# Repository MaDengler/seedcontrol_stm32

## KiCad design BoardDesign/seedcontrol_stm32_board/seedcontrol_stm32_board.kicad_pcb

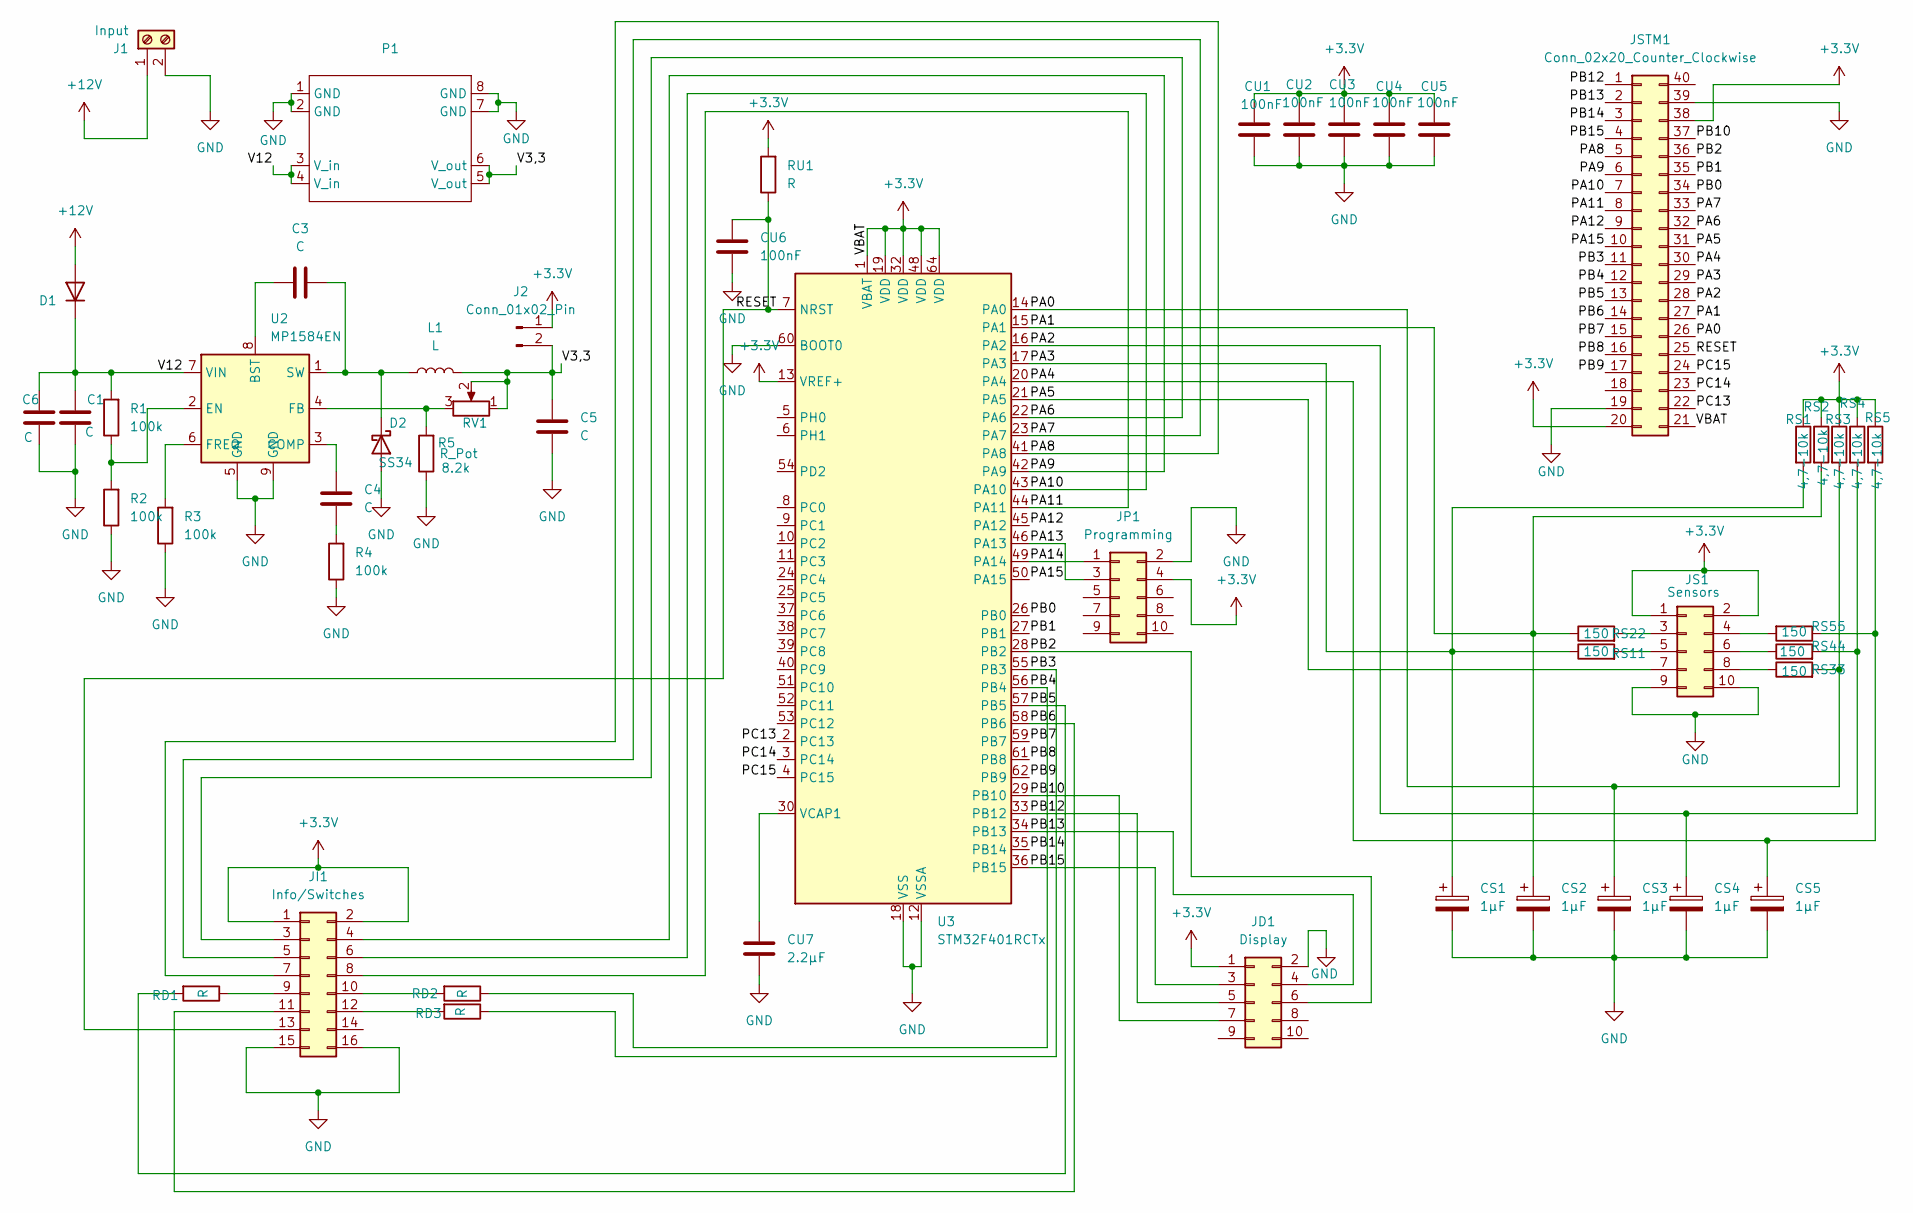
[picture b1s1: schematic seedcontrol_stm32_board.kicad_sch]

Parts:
C1, C3, C4: C; C_0603_1608Metric
C5, C6: C; C_1206_3216Metric
CS1, CS2, CS3, CS4, CS5: 1µF; C_Rect_L10.0mm_W3.0mm_P7.50mm_MKS4
CU1, CU2, CU3, CU4, CU5, CU6: 100nF; C_0402_1005Metric
CU7: 2.2µF; C_0402_1005Metric
D1: D_DO-41_SOD81_P12.70mm_Horizontal
D2: SS34; D_SMA
J1: Input; TerminalBlock_Altech_AK300-2_P5.00mm
J2: Conn_01x02_Pin; PinHeader_1x02_P2.54mm_Vertical
JD1: Display; PinHeader_2x05_P2.54mm_Vertical
JI1: Info/Switches; PinHeader_2x08_P2.54mm_Vertical
JP1: Programming; PinHeader_2x05_P2.54mm_Vertical
JS1: Sensors; PinHeader_2x05_P2.54mm_Vertical
JSTM1: Conn_02x20_Counter_Clockwise; STM32_Blackpill_header
L1: L; L_Bourns_SRP7028A_7.3x6.6mm
P1: Voltage_converter
R1, R2, R3, R4: 100k; R_0603_1608Metric
R5: 8.2k; R_0603_1608Metric
RD1, RD2, RD3: R; R_0603_1608Metric
RS1, RS2, RS3, RS4, RS5: 4,7-10k; R_Axial_DIN0309_L9.0mm_D3.2mm_P12.70mm_Horizontal
RS11, RS22, RS33, RS44, RS55: 150; R_Axial_DIN0309_L9.0mm_D3.2mm_P12.70mm_Horizontal
RU1: R; R_0603_1608Metric
RV1: R_Pot; Potentiometer_Bourns_TC33X_Vertical
U2: MP1584EN; SOIC-8-1EP_3.9x4.9mm_P1.27mm_EP2.62x3.51mm
U3: STM32F401RCTx; LQFP-64_10x10mm_P0.5mm

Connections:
+3.3V: CU1.2, CU2.2, CU3.2, CU4.2, CU5.2, J2.1, JD1.1, JI1.1, JI1.2, JP1.4, JS1.1, JS1.2, JSTM1.20, JSTM1.21, JSTM1.38, RS1.1, RS2.1, RS3.1, RS4.1, RS5.1, RU1.2, U3.1 (VBAT), U3.13 (VREF+), U3.19 (VDD), U3.32 (VDD), U3.48 (VDD), U3.64 (VDD)
+12V: D1.1 (A), J1.1
/PA0: CS3.1, JSTM1.26, RS3.2, RS33.2, U3.14 (PA0)
/PA1: CS2.1, JSTM1.27, RS2.2, RS22.1, U3.15 (PA1)
/PA2: CS4.1, JSTM1.28, RS4.2, RS44.2, U3.16 (PA2)
/PA3: CS1.1, JSTM1.29, RS1.2, RS11.1, U3.17 (PA3)
/PA4: CS5.1, JSTM1.30, RS5.2, RS55.1, U3.20 (PA4)
/PA5: JS1.7, JSTM1.31, U3.21 (PA5)
/PA6: JI1.3, JSTM1.32, U3.22 (PA6)
/PA7: JI1.5, JSTM1.33, U3.23 (PA7)
/PA8: JI1.7, JSTM1.5, U3.41 (PA8)
/PA9: JI1.4, JSTM1.6, U3.42 (PA9)
/PA10: JI1.6, JSTM1.7, U3.43 (PA10)
/PA11: JI1.8, JSTM1.8, U3.44 (PA11)
/PA12: JSTM1.9, U3.45 (PA12)
/PA13: JP1.3, U3.46 (PA13)
/PA14: JP1.1, U3.49 (PA14)
/PA15: JSTM1.10, U3.50 (PA15)
/PB0: JSTM1.34, U3.26 (PB0)
/PB1: JSTM1.35, U3.27 (PB1)
/PB2: JD1.6, JSTM1.36, U3.28 (PB2)
/PB3: JSTM1.11, RD3.1, U3.55 (PB3)
/PB4: JSTM1.12, RD2.1, U3.56 (PB4)
/PB5: JSTM1.13, RD1.2, U3.57 (PB5)
/PB6: JI1.11, JSTM1.14, U3.58 (PB6)
/PB7: JSTM1.15, U3.59 (PB7)
/PB8: JSTM1.16, U3.61 (PB8)
/PB9: JSTM1.17, U3.62 (PB9)
/PB10: JD1.7, JSTM1.37, U3.29 (PB10)
/PB12: JD1.5, JSTM1.1, U3.33 (PB12)
/PB13: JD1.4, JSTM1.2, U3.34 (PB13)
/PB14: JSTM1.3, U3.35 (PB14)
/PB15: JD1.3, JSTM1.4, U3.36 (PB15)
/PC13: JSTM1.22, U3.2 (PC13)
/PC14: JSTM1.23, U3.3 (PC14)
/PC15: JSTM1.24, U3.4 (PC15)
/RESET: CU6.2, JI1.13, JSTM1.25, RU1.1, U3.7 (NRST)
/V3,3: C5.2, J2.2, L1.2, P1.5 (V_out), P1.6 (V_out), RV1.1, RV1.2
/V12: C1.2, C6.2, D1.2 (K), P1.3 (V_in), P1.4 (V_in), R1.2, U2.7 (VIN)
GND: C1.1, C5.1, C6.1, CS1.2, CS2.2, CS3.2, CS4.2, CS5.2, CU1.1, CU2.1, CU3.1, CU4.1, CU5.1, CU6.1, CU7.1, D2.2 (A), J1.2, JD1.2, JI1.15, JI1.16, JP1.2, JS1.9, JS1.10, JSTM1.19, JSTM1.39, P1.1 (GND), P1.2 (GND), P1.7 (GND), P1.8 (GND), R2.1, R3.1, R4.1, R5.1, U2.5 (GND), U2.9 (GND), U3.12 (VSSA), U3.18 (VSS), U3.31 (VSS), U3.47 (VSS), U3.60 (BOOT0), U3.63 (VSS)
unnamed: C4.1, R4.2
unnamed: C3.2, D2.1 (K), L1.1, U2.1 (SW)
unnamed: JI1.9, RD1.1
unnamed: JI1.10, RD2.2
unnamed: JI1.12, RD3.2
unnamed: JS1.3, RS22.2
unnamed: JS1.4, RS55.2
unnamed: JS1.5, RS11.2
unnamed: JS1.6, RS44.1
unnamed: JS1.8, RS33.1
unnamed: C3.1, U2.8 (BST)
unnamed: C4.2, U2.3 (COMP)
unnamed: R1.1, R2.2, U2.2 (EN)
unnamed: R5.2, RV1.3, U2.4 (FB)
unnamed: R3.2, U2.6 (FREQ)
unnamed: CU7.2, U3.30 (VCAP1)

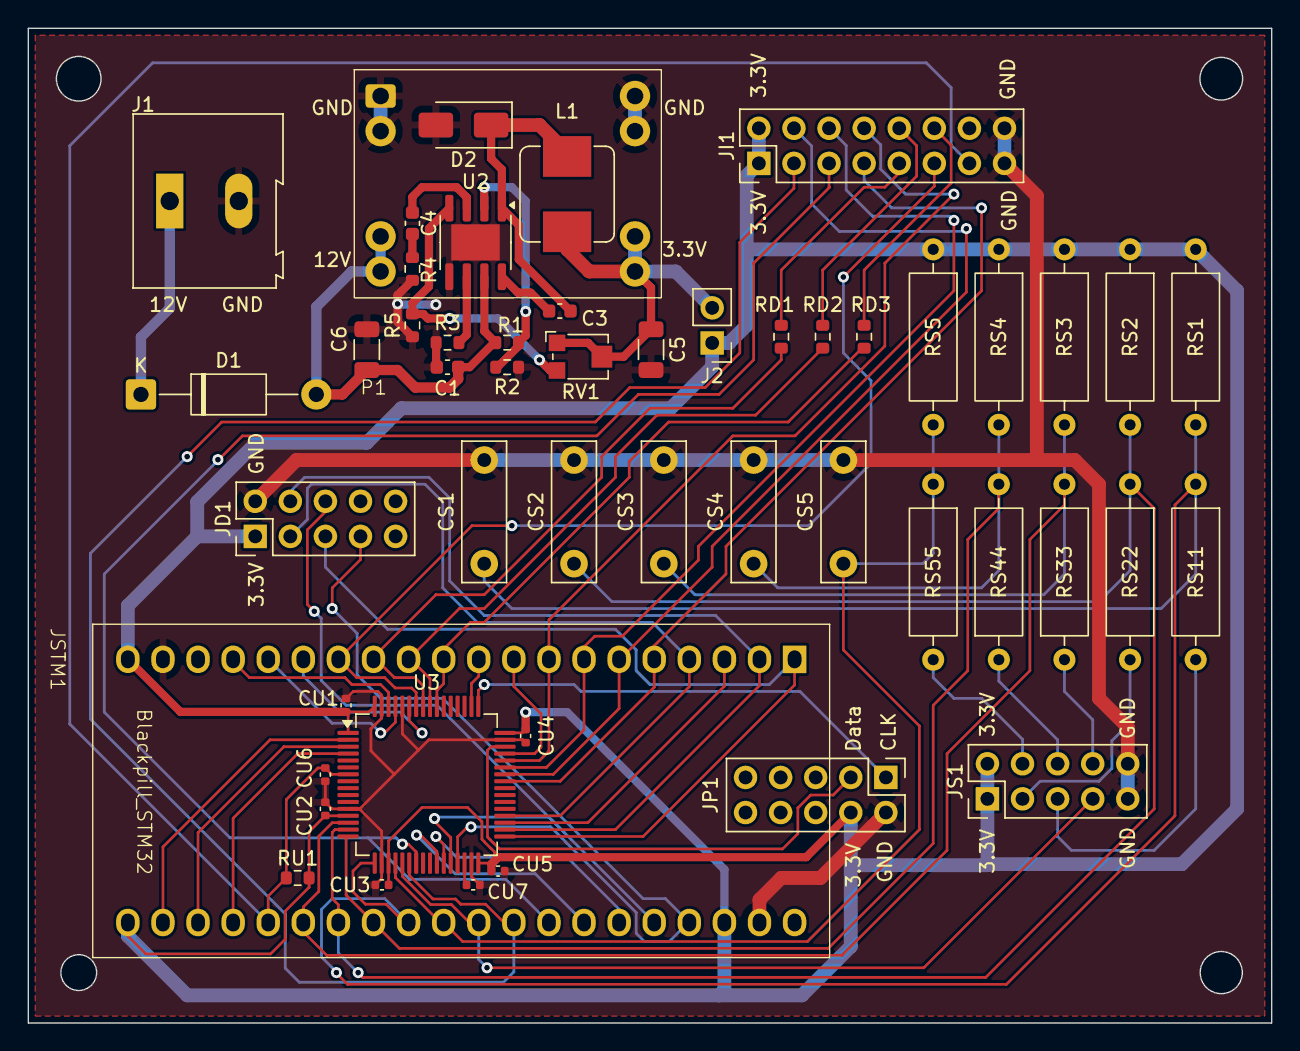
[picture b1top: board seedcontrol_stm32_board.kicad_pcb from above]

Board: 2 copper layers, 90.0 x 72.0 mm, 50 parts (0 on the bottom side), 56 nets.

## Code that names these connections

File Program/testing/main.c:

#include "stm32f4xx.h"
#include <stdint.h>
#include <stdbool.h>

/*
 * Test-Harness for seedcontrol_stm32
 * 
 * Pin mapping (Tester → Seedcontrol):
 *   PA0 → PA0  (Wheel sensor)
 *   PA1 → PA1  (Seeder 1)
 *   PA2 → PA2  (Seeder 2)
 *   PA3 → PA3  (Seeder 3)
 *   PA4 → PA4  (Seeder 4)
 *   PA5 → PA5  (Fan pulses / TIM2 ext clock)
 *
 * All outputs directly active low (accent) via pulldown.
 * Active low pulse of ~1ms.
 */

#define PIN_WHEEL   GPIO_ODR_OD0
#define PIN_SEEDER1 GPIO_ODR_OD1
#define PIN_SEEDER2 GPIO_ODR_OD2
#define PIN_SEEDER3 GPIO_ODR_OD3
#define PIN_SEEDER4 GPIO_ODR_OD4
#define PIN_FAN     GPIO_ODR_OD5
#define PIN_ALL_SEEDERS (PIN_SEEDER1 | PIN_SEEDER2 | PIN_SEEDER3 | PIN_SEEDER4)

static volatile uint32_t ticks;

void SysTick_Handler(void){
    ticks++;
}

static void systick_init(void){
    SysTick_Config(16000); // 1ms @ 16MHz HSI
    ticks = 0;
}

static void delay_ms(uint32_t ms){
    uint32_t start = ticks;
    while((ticks - start) < ms);
}

static void pulse_low(uint32_t pins, uint32_t duration_ms) __attribute__((unused));
static void pulse_low(uint32_t pins, uint32_t duration_ms){
    GPIOA->ODR &= ~pins;
    delay_ms(duration_ms);
    GPIOA->ODR |= pins;
    delay_ms(1);
}

static void gpio_init(void){
    RCC->AHB1ENR |= RCC_AHB1ENR_GPIOAEN;
    // PA0-PA5 as push-pull outputs
    GPIOA->MODER &= ~(GPIO_MODER_MODER0 | GPIO_MODER_MODER1 | GPIO_MODER_MODER2 |
                       GPIO_MODER_MODER3 | GPIO_MODER_MODER4 | GPIO_MODER_MODER5);
    GPIOA->MODER |= GPIO_MODER_MODER0_0 | GPIO_MODER_MODER1_0 | GPIO_MODER_MODER2_0 |
                     GPIO_MODER_MODER3_0 | GPIO_MODER_MODER4_0 | GPIO_MODER_MODER5_0;
    // Start all high (seedcontrol inputs have pull-ups, falling edge triggers)
    GPIOA->ODR |= PIN_WHEEL | PIN_ALL_SEEDERS | PIN_FAN;
}

int main(void){
    gpio_init();
    systick_init();
    delay_ms(500); // Wait for seedcontrol to boot


    while(1){

        for(int i = 0; i < 65; i++){
            delay_ms(800);
            pulse_low(PIN_WHEEL, 80); // Simulate wheel rotation
            delay_ms(80);
            pulse_low(PIN_SEEDER1, 50); // Simulate seeder 1 active
            pulse_low(PIN_SEEDER2, 50); // Simulate seeder 2 active
            pulse_low(PIN_SEEDER3, 50); // Simulate seeder 3 active
            pulse_low(PIN_SEEDER4, 50); // Simulate seeder 4 active
            delay_ms(800);
            pulse_low(PIN_WHEEL, 80); // Simulate wheel rotation

            delay_ms(80);
        }
        for(int i = 0; i < 250; i++){
            pulse_low(PIN_FAN, 5); // Simulate fan rotation
            delay_ms(15);
        }
    }

    return 0;

}

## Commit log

2025-03-14 Initial commit. Set up project structure and Build with Makefile. Example program that blinks an LED connected to Pin C13 working
2025-03-14 Added gitignore to exclude build directory
2025-03-16 Implemented display function
2025-03-16 Changed main such that the fan-symbol is blinking on display
2025-03-16 Adjusted SPI initialisation
2025-03-16 Added .vscode to gitignore
2025-03-17 Put all programm files into a separate folder to keep it separated from the hardware stuff.
2025-03-19 Adjusted SPI baudrate such that communication is more stable. No display errors could be observed with the new baudrate.
2025-03-20 Started designing of the board. Added status struct that holds the current state of the machine.
2025-03-30 Added KiCAD schematic of the board and startet designing the PCB layout.
2025-04-06 Finalized board layout.
2025-04-16 Interrupts and timers are working as expected and state is displayed correxctly. Alarm, status LEDs and prsisting of the counter states needs to be implemented.
2025-04-19 Implemented storing of data in flash memory.
2025-09-20 Functional state, but needs work.
2026-03-11 Changed board design. Added footprint for STM32_Blackpill connector.
2026-03-14 Finalized schematics. Placed all components in Boardview.
2026-03-22 Final Board design.
2026-03-26 Reworked persist logic such that the whole sector 5 is used in oder to reduce number of erasions.
2026-04-06 Persist does now not erase on every write to flash. Also issues with false alarms have been eliminated by considering the previous seederStates and adding alarm prevent during the first wheel rotatio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
2026-04-06 Removed unnecessary bin file dumps that were downloaded from the microcontroller.
2026-04-07 Moved initialisation of state struct into state_init. Optimized button press and alarm, such that no delays block the main loop.
2026-04-10 Added mute for the alarm tone for the whole cycle by longpressing the button in alarm state.
2026-04-17 Copied Freecad design folder for the housing from previous seedcontrol project into here.
